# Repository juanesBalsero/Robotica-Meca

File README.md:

# Robotica-Meca
El proyecto consiste en la creación de una planta de embalaje de medicamentos compuesta por 5 brazos roboticos, sub dividido en diferentes grupos de trabajo deacuerdo a cada robot

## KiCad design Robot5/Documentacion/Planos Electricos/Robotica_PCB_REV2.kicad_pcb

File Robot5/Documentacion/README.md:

Contiene información respecto al Robot5, encargado de agarrar la caja con medicamento y tapa y apilarla en una mesa exterior en la que se irán apilando múltiples cajas.

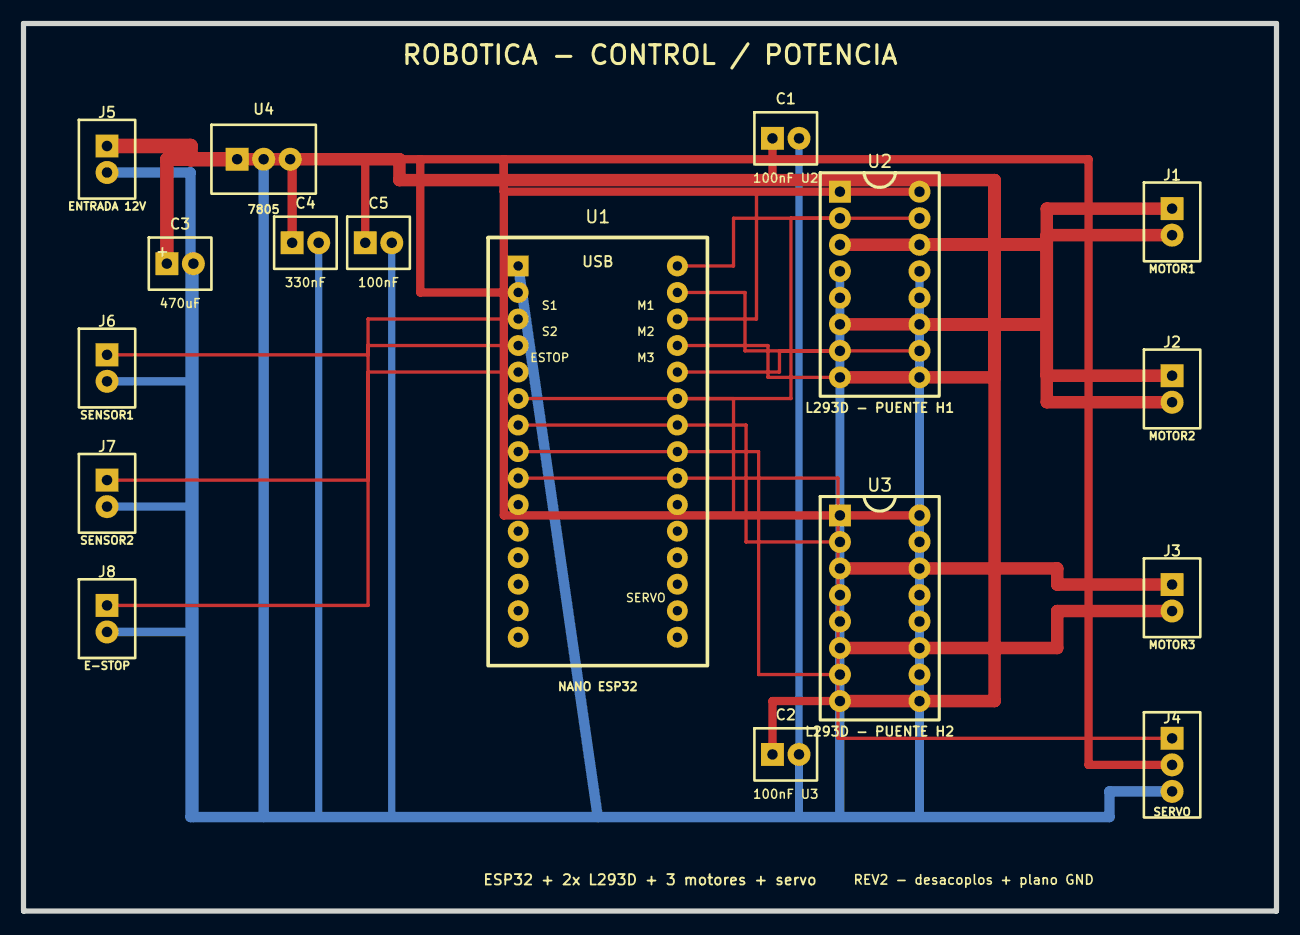
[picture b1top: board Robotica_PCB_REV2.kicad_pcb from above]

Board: 2 copper layers, 120.0 x 85.0 mm, 17 parts (0 on the bottom side), 22 nets.

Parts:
C1: 100nF U2; C_Disc
C2: 100nF U3; C_Disc
C3: 470uF; CP_Radial
C4: 330nF; C_Disc
C5: 100nF; C_Disc
J1: MOTOR1; Conn_2
J2: MOTOR2; Conn_2
J3: MOTOR3; Conn_2
J4: SERVO; Conn_3
J5: ENTRADA 12V; Conn_2
J6: SENSOR1; Conn_2
J7: SENSOR2; Conn_2
J8: E-STOP; Conn_2
U1: NANO ESP32; NANO_ESP32_GENERIC_2x15
U2: L293D - PUENTE H1; DIP-16_W7.62
U3: L293D - PUENTE H2; DIP-16_W7.62
U4: 7805; TO220-3

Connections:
+5V: C1.1, C2.1, C5.1, J4.2, U1.2, U2.16, U3.16, U4.3
+12V: C3.1, C4.1, J5.1, U2.8, U3.8, U4.1
ESTOP: J8.1, U1.5
GND: C1.2, C2.2, C3.2, C4.2, C5.2, J4.3, J5.2, J6.2, J7.2, J8.2, U1.1, U2.4, U2.5, U2.12, U2.13, U3.4, U3.5, U3.9, U3.10, U3.12, U3.13, U3.15, U4.2
M1_A: J1.1, U2.3
M1_B: J1.2, U2.6
M1_EN: U1.18, U2.1
M1_IN1: U1.16, U2.2
M1_IN2: U1.17, U2.7
M2_A: J2.1, U2.11
M2_B: J2.2, U2.14
M2_EN: U1.19, U2.9
M2_IN3: U1.20, U2.10
M2_IN4: U1.21, U2.15
M3_A: J3.1, U3.3
M3_B: J3.2, U3.6
M3_EN: U1.6, U3.1
M3_IN1: U1.7, U3.2
M3_IN2: U1.8, U3.7
SENSOR1: J6.1, U1.3
SENSOR2: J7.1, U1.4
SERVO_PWM: J4.1, U1.9
